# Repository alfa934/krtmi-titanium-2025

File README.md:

# 🤖TITANIUM (KRTMI) 2025 🤖

<p align="center"><b>📌Logo EIRRG dan TITANIUM📌</b></p>

## Deskripsi 📚
Kami adalah tim KRTMI (Kontes Robot Tematik Indonesia) dari Telkom University.  <br>
TITANIUM adalah nama tim kami.

## Anggota TITANIUM 2025 🏃‍♂️🏃‍♀️
| No | Nama | Nim | Jobdesk |
| :---: | :--- | :---: | :---: |
| 1 | Iki Tayubi | 1102223031 | Elektronika |
| 2 | Muhammad Aushaf Al Farras | 1102210215 | Program |
| 3 | Ahmad Fadhil Ghifari Ekaputra | 1102210053 | Program |
| 4 | Nabilla Rahma Anasya | 1104220025 | Official |
| 5 | Febrian Josua Kontu | 1102223066 | Program |
| 6 | Zahrani Cahya Priesa | 1103223074 | Official |
| 7 | Nurlina Sari | 1102223038 | Mekanik |
| 8 | Sarah Alexandra Siahaan | 1101220277 | Official |
| 9 | Muhammad Irfan Nabil | 1102223109 | Elektronika |
| 10 | Dimas Dwi Septian | 1102223106 | Mekanik |
| 11 | Muh. Ihksan Hatta | 1101223186 | Official |
| 12 | Valentine Rusliani Febriana | 102012300364 | Official |
| 13 | Ihsan Lisanul Arifin | 101022300309 | Mekanik |
| 14 | Muhammad Syauqi Fakhri | 101022330026 | Elektronika |
| 15 | Muhammad Miftah Faqih | 101022330177 | Program |
| 16 | Ivander Sugiarta Halim | 101022330111 | Elektronika |
| 17 | Mohammad Dzakwan Darrell Rifqi | 103032330138 | Program |
| 18 | Raditya Satria Pratama | 101032300096 | Program |
| 19 | Mohammad Hasbi Ashidiqi | 101022330302 | Mekanik |
| 20 | Raffa Ilyasa | 101022400260 | Elektronika |
| 21 | Wisnu Klana | 101022400118 | Official | 
| 22 | Brightly Jonah Aditya Santosa Padmohoetomo | 101022400074 | Program |
| 23 | Vincentius Radithya Evan Pratomo | 101062300011 | Mekanik | 

## Dosen Pembimbing 👨‍🏫👩‍🏫
| Pembimbing | Nama |
| :--- | :--- |
| Pembimbing 1 | Agung Surya Wibowo ,S.T.,M.T., Ph.D |
| Pembimbing 2 | Basith Abdurrohman Asy'ari, S.Tr.T., M.T. |

## KRTMI 2025 ??????
Tema : ?????? <br>
Jumlah Robot : ?????

## Sejarah KRTMI 📜
KRTMI pertama kali muncul tahun 2019, dan saat ini muncul 4 tema baru dari 2019 - 2024. <br>
Tujuannya untuk menyelesaikan masalah-masalah yang ada di Indonesia dengan teknologi bidang robotika.

## KRTMI 2024 (Robot Memilah Sampah) 🚮

Untuk lebih jelas, baca [Buku Panduan 2024](https://dit-mawa.upi.edu/wp-content/uploads/2024/01/Buku-Pedoman-KRI-2024-fix.pdf) halaman 133
### Video krtmi 2024
 <br>

## KRTMI 2021 - 2023 (Robo Game – Digital Twin) 🤖💻

Untuk lebih jelas, baca [Buku Panduan 2023](https://kontesrobotindonesia.id/data/2023/BukuPedomanKRI2023.pdf) halaman 125
### Video krtmi 2023
 <br>

## KRTMI 2020 (Robot Kesehatan) 😷👨‍⚕️👩‍⚕️

Untuk lebih jelas baca [Buku Panduan 2020](https://kontesrobotindonesia.id/data/2020/PetunjukPelaksanaanKRIDaring2020.pdf) halaman 79
### Video krtmi 2020
 <br>

## KRTMI 2019 (Robot Pertanian Padi) 🍚🌾

Untuk lebih jelas, baca [Buku Panduan 2019](https://kontesrobotindonesia.id/data/2019/Panduan_KRTMI2019.pdf) 
### Video krtmi 2019
 <br>

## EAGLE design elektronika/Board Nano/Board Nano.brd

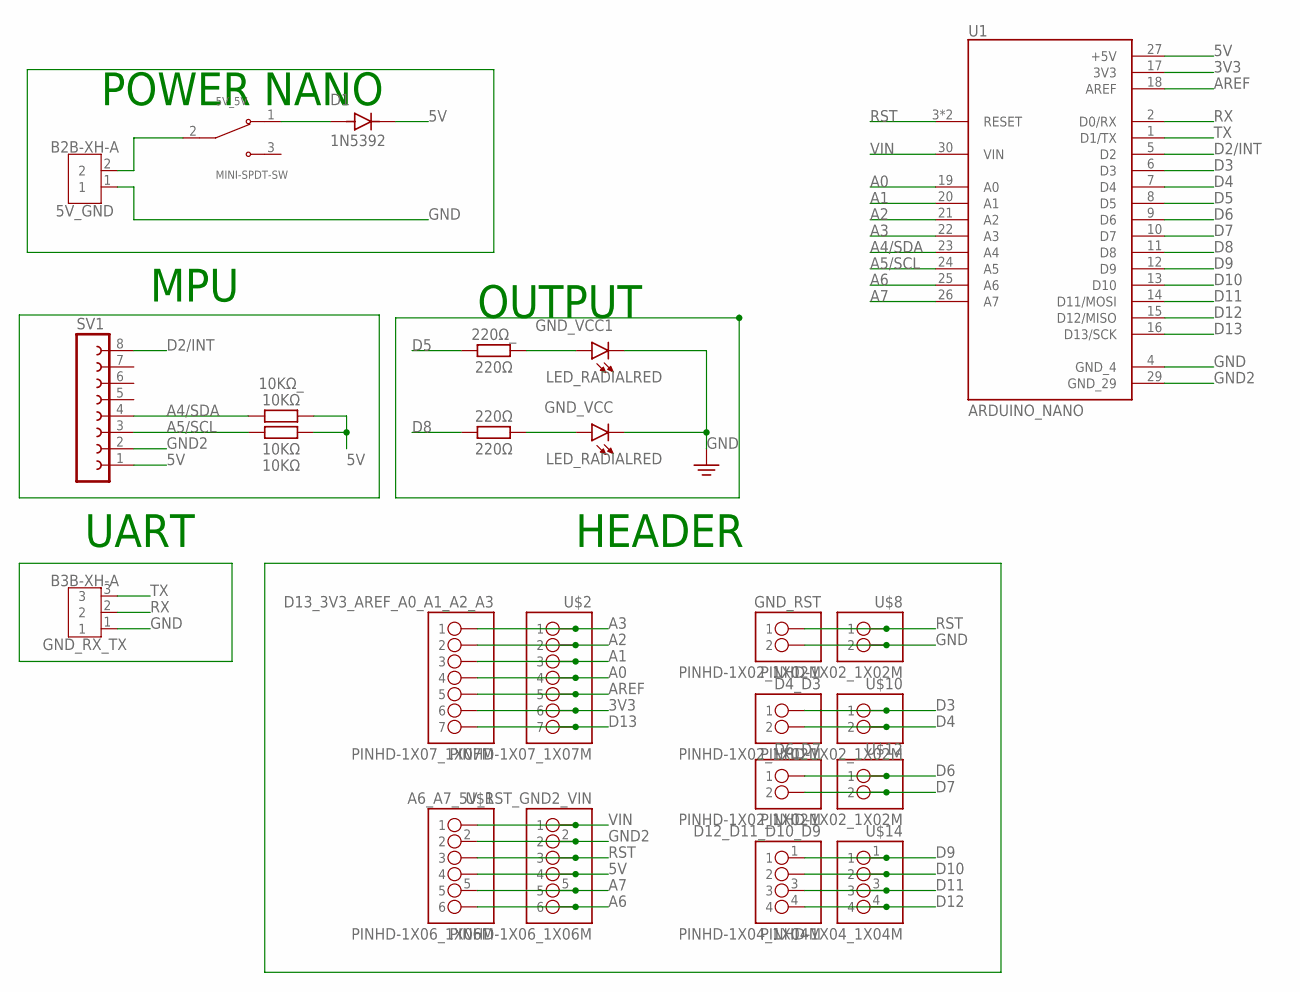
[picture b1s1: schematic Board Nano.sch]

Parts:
5V_5V: MINI-SPDT-SW; SW_MINI-SPDT-SW
5V_GND: B2B-XH-A
10KΩ, 10KΩ_: 10KΩ; RESAD1176W63L850D250B
220Ω, 220Ω_: 220Ω; RESAD1176W63L850D250B
A6_A7_5V_RST_GND2_VIN: PINHD-1X06_1X06M; 1X06
D1: 1N5392; DIOAD1300W80L670D310
D4_D3, D6_D7: PINHD-1X02_1X02M; 1X02
D12_D11_D10_D9: PINHD-1X04_1X04M; 1X04
D13_3V3_AREF_A0_A1_A2_A3: PINHD-1X07_1X07M; 1X07
GND_RST: PINHD-1X02_1X02M; 1X02
GND_RX_TX: B3B-XH-A
GND_VCC, GND_VCC1: LED_RADIALRED; LEDRD254W60D565H860B_R
SV1: FE08-1; FE08
U1: ARDUINO_NANO; MODULE_ARDUINO_NANO
U$1: PINHD-1X06_1X06M; 1X06
U$2: PINHD-1X07_1X07M; 1X07
U$8, U$10, U$12: PINHD-1X02_1X02M; 1X02
U$14: PINHD-1X04_1X04M; 1X04

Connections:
3V3: D13_3V3_AREF_A0_A1_A2_A3.6, U1.17 (3V3), U$2.6
5V: 10KΩ.2, 10KΩ_.2, A6_A7_5V_RST_GND2_VIN.4, D1.C (K), SV1.1, U1.27 (+5V), U$1.4
5V_FB: 5V_5V.2, 5V_GND.2
A0: D13_3V3_AREF_A0_A1_A2_A3.4, U1.19 (A0), U$2.4
A1: D13_3V3_AREF_A0_A1_A2_A3.3, U1.20 (A1), U$2.3
A2: D13_3V3_AREF_A0_A1_A2_A3.2, U1.21 (A2), U$2.2
A3: D13_3V3_AREF_A0_A1_A2_A3.1, U1.22 (A3), U$2.1
A4/SDA: 10KΩ_.1, SV1.4, U1.23 (A4)
A5/SCL: 10KΩ.1, SV1.3, U1.24 (A5)
A6: A6_A7_5V_RST_GND2_VIN.6, U1.25 (A6), U$1.6
A7: A6_A7_5V_RST_GND2_VIN.5, U1.26 (A7), U$1.5
AREF: D13_3V3_AREF_A0_A1_A2_A3.5, U1.18 (AREF), U$2.5
D2/INT: SV1.8, U1.5 (D2)
D3: D4_D3.1, U1.6 (D3), U$10.1
D4: D4_D3.2, U1.7 (D4), U$10.2
D5: 220Ω_.1, U1.8 (D5)
D6: D6_D7.1, U1.9 (D6), U$12.1
D7: D6_D7.2, U1.10 (D7), U$12.2
D8: 220Ω.1, U1.11 (D8)
D9: D12_D11_D10_D9.1, U1.12 (D9), U$14.1
D10: D12_D11_D10_D9.2, U1.13 (D10), U$14.2
D11: D12_D11_D10_D9.3, U1.14 (D11/MOSI), U$14.3
D12: D12_D11_D10_D9.4, U1.15 (D12/MISO), U$14.4
D13: D13_3V3_AREF_A0_A1_A2_A3.7, U1.16 (D13/SCK), U$2.7
GND: 5V_GND.1, GND_RST.2, GND_RX_TX.1, GND_VCC.C, GND_VCC1.C, U1.4 (GND_4), U$8.2
GND2: A6_A7_5V_RST_GND2_VIN.2, SV1.2, U1.29 (GND_29), U$1.2
unnamed: 220Ω_.2, GND_VCC1.A
unnamed: 220Ω.2, GND_VCC.A
unnamed: 5V_5V.1, D1.A
RST: A6_A7_5V_RST_GND2_VIN.3, GND_RST.1, U1.3 (RESET), U1.28 (RESET), U$1.3, U$8.1
RX: GND_RX_TX.2, U1.2 (D0/RX)
TX: GND_RX_TX.3, U1.1 (D1/TX)
VIN: A6_A7_5V_RST_GND2_VIN.1, U1.30 (VIN), U$1.1

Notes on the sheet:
POWER NANO
MPU
UART
OUTPUT
HEADER

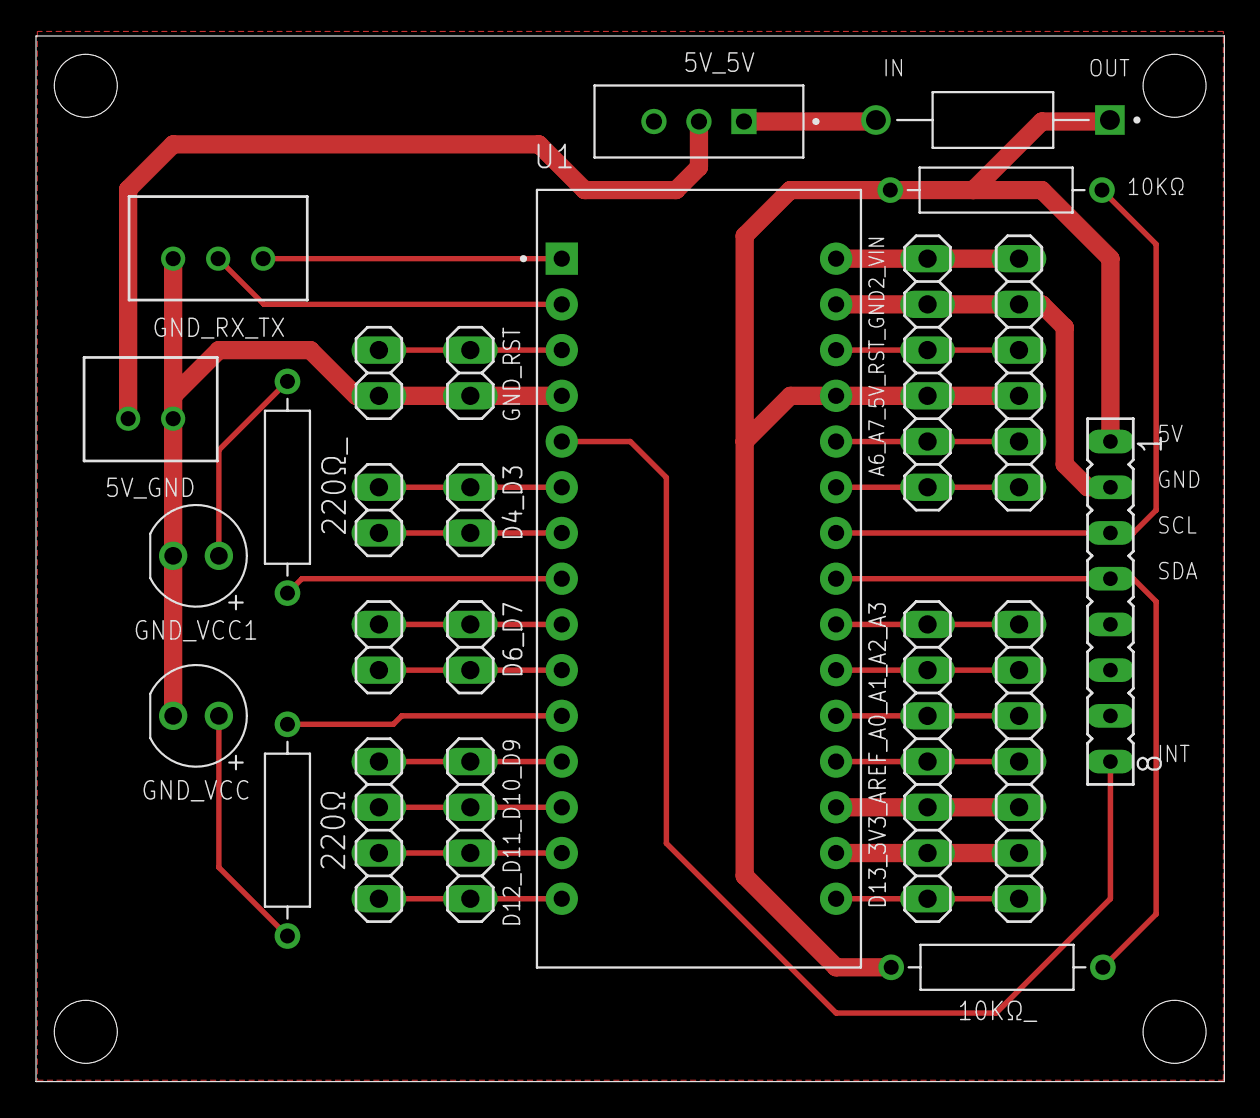
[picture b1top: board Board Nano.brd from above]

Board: 2 copper layers, 66.0 x 58.1 mm, 24 parts (0 on the bottom side), 33 nets.

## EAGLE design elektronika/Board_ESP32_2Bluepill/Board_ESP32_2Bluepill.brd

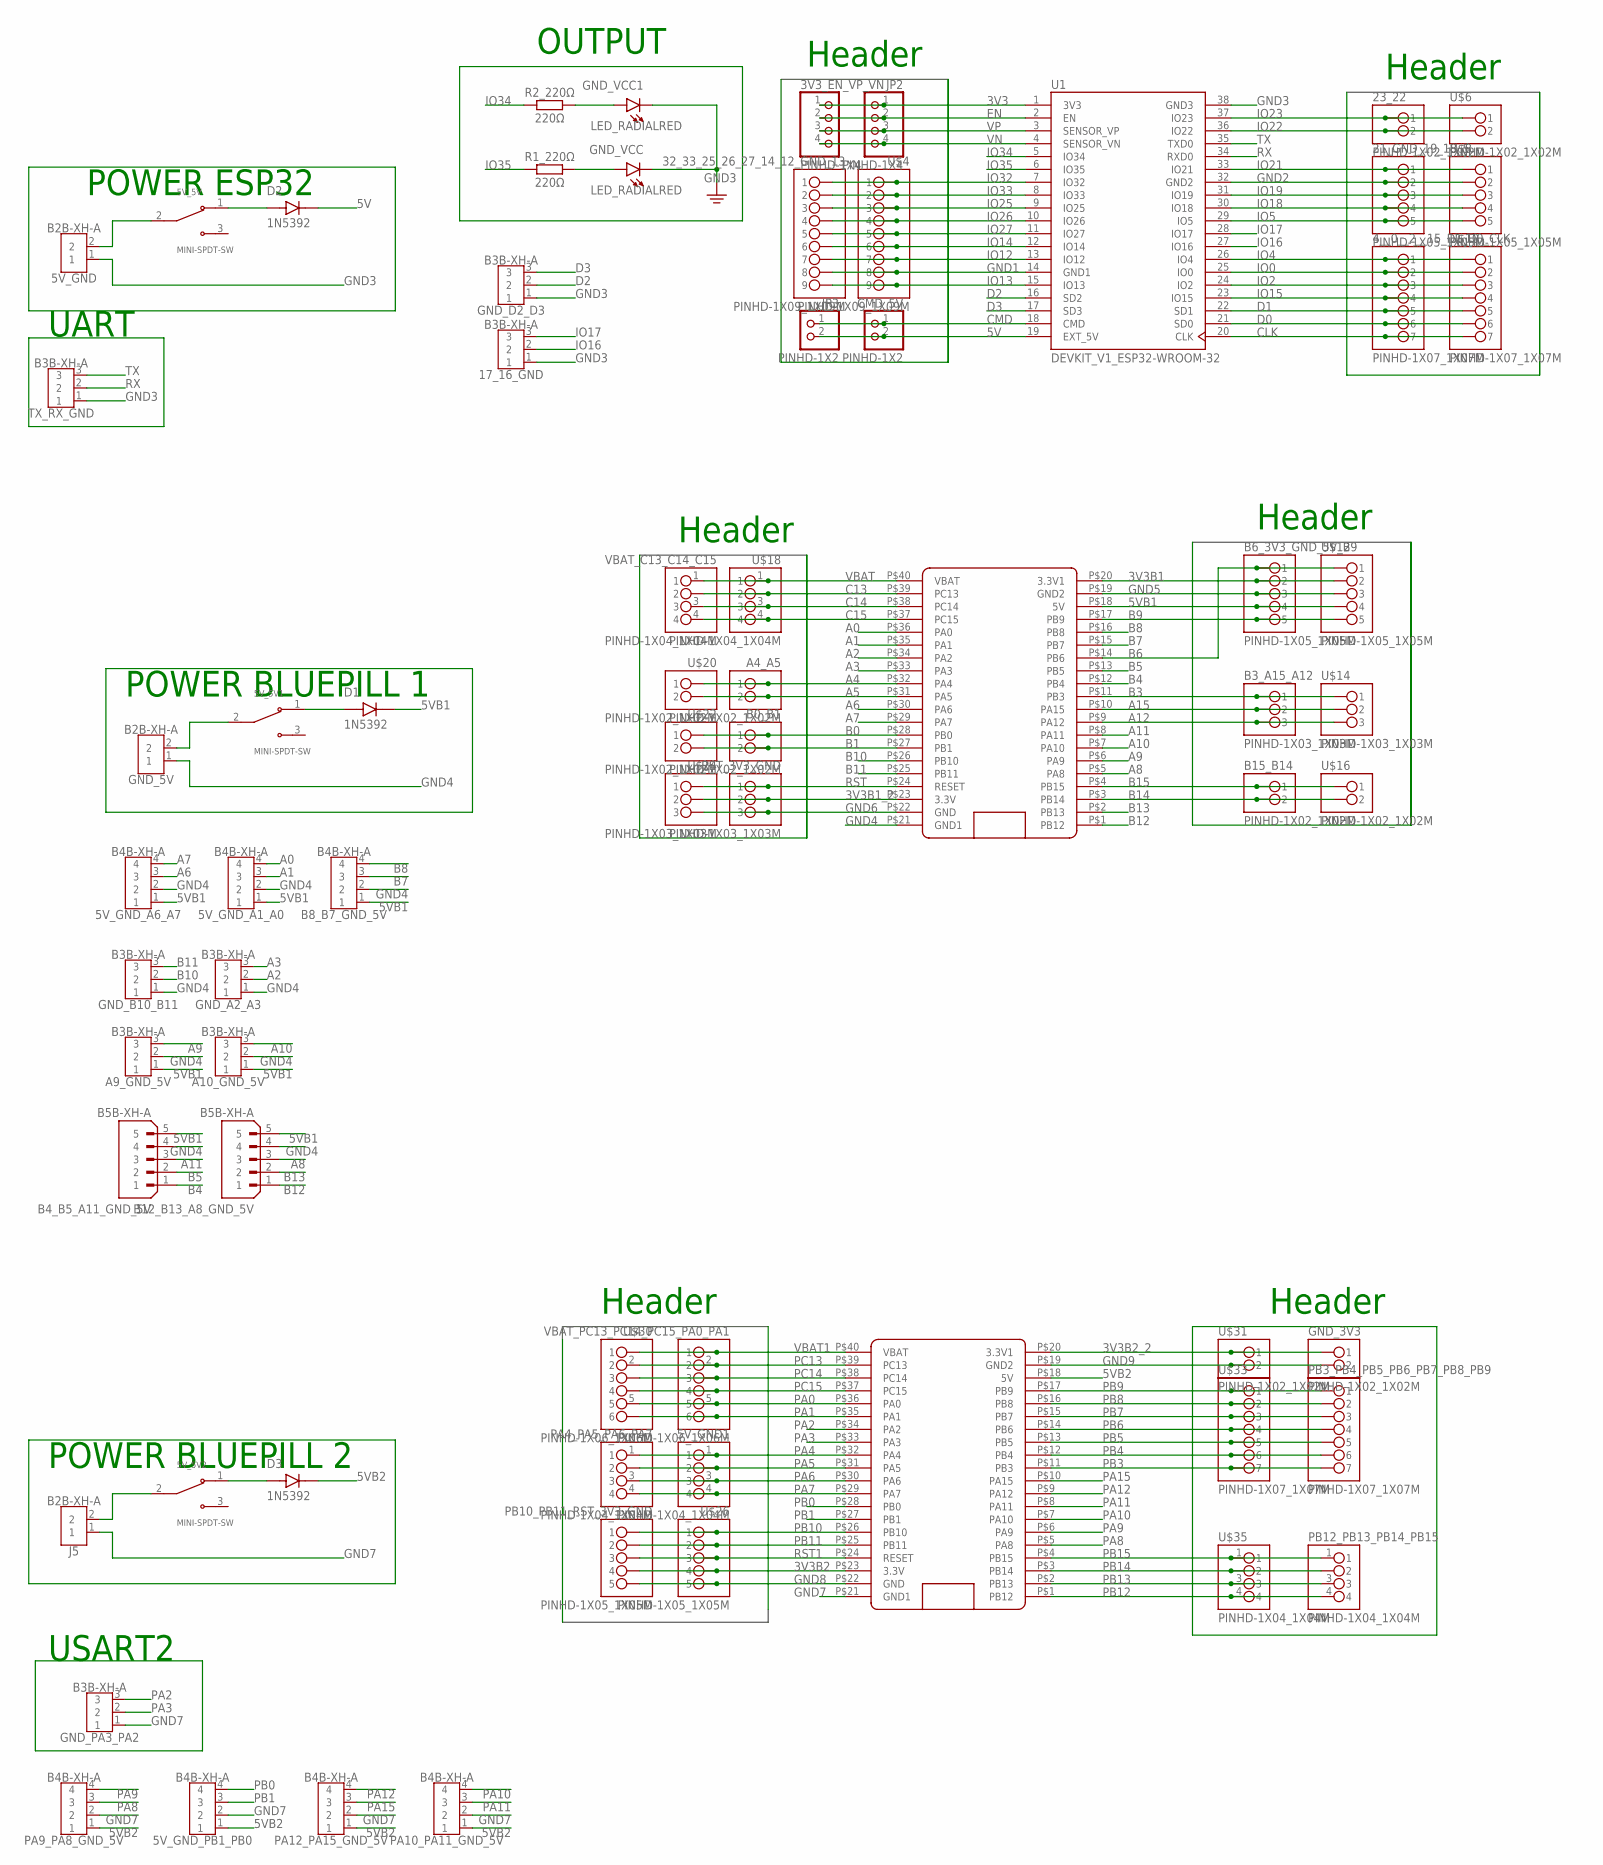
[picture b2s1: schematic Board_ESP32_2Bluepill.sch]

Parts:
3V3_EN_VP_VN: PINHD-1X4; 1X04
4__0__2__15_D1_D0_CLK: PINHD-1X07_1X07M; 1X07
5V_5V, 5V_5V1, 5V_5V2: MINI-SPDT-SW; SW_MINI-SPDT-SW
5V_GND: B2B-XH-A
5V_GND1: PINHD-1X04_1X04M; 1X04
5V_GND_A1_A0, 5V_GND_A6_A7, 5V_GND_PB1_PB0: B4B-XH-A
17_16_GND: B3B-XH-A
21_GND_19_18_5: PINHD-1X05_1X05M; 1X05
23_22: PINHD-1X02_1X02M; 1X02
32_33_25_26_27_14_12_GND_13: PINHD-1X09_1X09M; 1X09
A4_A5: PINHD-1X02_1X02M; 1X02
A9_GND_5V, A10_GND_5V: B3B-XH-A
B0_B1, B15_B14: PINHD-1X02_1X02M; 1X02
B3_A15_A12: PINHD-1X03_1X03M; 1X03
B4_B5_A11_GND_5V, B12_B13_A8_GND_5V: B5B-XH-A; JST_B5B-XH-A
B6_3V3_GND_5V_B9: PINHD-1X05_1X05M; 1X05
B8_B7_GND_5V: B4B-XH-A
CMD_5V: PINHD-1X2; 1X02
D1, D2, D3: 1N5392; DIOAD1300W80L670D310
GND_3V3: PINHD-1X02_1X02M; 1X02
GND_5V: B2B-XH-A
GND_A2_A3: B3B-XH-A
GND_B10_B11: B3B-XH-A
GND_D2_D3: B3B-XH-A
GND_PA3_PA2: B3B-XH-A
GND_VCC, GND_VCC1: LED_RADIALRED; LEDRD254W60D565H860B_R
J5: B2B-XH-A
JP2: PINHD-1X4; 1X04
JP3: PINHD-1X2; 1X02
PA4_PA5_PA6_PA7: PINHD-1X04_1X04M; 1X04
PA9_PA8_GND_5V, PA10_PA11_GND_5V, PA12_PA15_GND_5V: B4B-XH-A
PB3_PB4_PB5_PB6_PB7_PB8_PB9: PINHD-1X07_1X07M; 1X07
PB10_PB11_RST_3V3_GND: PINHD-1X05_1X05M; 1X05
PB12_PB13_PB14_PB15: PINHD-1X04_1X04M; 1X04
R1_220Ω, R2_220Ω: 220Ω; RESAD1176W63L850D250B
RST_3V3_GND: PINHD-1X03_1X03M; 1X03
TX_RX_GND: B3B-XH-A
U1: DEVKIT_V1_ESP32-WROOM-32; MODULE_DEVKIT_V1_ESP32-WROOM-32
U$1, U$2: BLUE_PILL
U$4: PINHD-1X09_1X09M; 1X09
U$6, U$16, U$20, U$22, U$31: PINHD-1X02_1X02M; 1X02
U$8, U$12, U$26: PINHD-1X05_1X05M; 1X05
U$10, U$33: PINHD-1X07_1X07M; 1X07
U$14, U$24: PINHD-1X03_1X03M; 1X03
U$18, U$35: PINHD-1X04_1X04M; 1X04
U$30: PINHD-1X06_1X06M; 1X06
VBAT_C13_C14_C15: PINHD-1X04_1X04M; 1X04
VBAT_PC13_PC14_PC15_PA0_PA1: PINHD-1X06_1X06M; 1X06

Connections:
3V3: 3V3_EN_VP_VN.1, JP2.1, U1.1 (3V3)
3V3B1: B6_3V3_GND_5V_B9.2, U$1.P$20 (3.3V1), U$12.2
3V3B1_2: RST_3V3_GND.2, U$1.P$23 (3.3V), U$24.2
3V3B2: PB10_PB11_RST_3V3_GND.4, U$2.P$23 (3.3V), U$26.4
3V3B2_2: GND_3V3.1, U$2.P$20 (3.3V1), U$31.1
5V: CMD_5V.2, D2.C (K), JP3.2, U1.19 (EXT_5V)
5VB1: 5V_GND_A1_A0.1, 5V_GND_A6_A7.1, A9_GND_5V.1, A10_GND_5V.1, B4_B5_A11_GND_5V.5, B6_3V3_GND_5V_B9.4, B8_B7_GND_5V.1, B12_B13_A8_GND_5V.5, D1.C (K), U$1.P$18 (5V), U$12.4
5VB2: 5V_GND_PB1_PB0.1, D3.C (K), PA9_PA8_GND_5V.1, PA10_PA11_GND_5V.1, PA12_PA15_GND_5V.1, U$2.P$18 (5V)
5V_FB1: 5V_5V.2, 5V_GND.2
5V_FB2: 5V_5V1.2, GND_5V.2
5V_FB3: 5V_5V2.2, J5.2
A0: 5V_GND_A1_A0.4, U$1.P$36 (PA0)
A1: 5V_GND_A1_A0.3, U$1.P$35 (PA1)
A2: GND_A2_A3.2, U$1.P$34 (PA2)
A3: GND_A2_A3.3, U$1.P$33 (PA3)
A4: A4_A5.1, U$1.P$32 (PA4), U$20.1
A5: A4_A5.2, U$1.P$31 (PA5), U$20.2
A6: 5V_GND_A6_A7.3, U$1.P$30 (PA6)
A7: 5V_GND_A6_A7.4, U$1.P$29 (PA7)
A8: B12_B13_A8_GND_5V.3, U$1.P$5 (PA8)
A9: A9_GND_5V.3, U$1.P$6 (PA9)
A10: A10_GND_5V.3, U$1.P$7 (PA10)
A11: B4_B5_A11_GND_5V.3, U$1.P$8 (PA11)
A12: B3_A15_A12.3, U$1.P$9 (PA12), U$14.3
A15: B3_A15_A12.2, U$1.P$10 (PA15), U$14.2
B0: B0_B1.1, U$1.P$28 (PB0), U$22.1
B1: B0_B1.2, U$1.P$27 (PB1), U$22.2
B3: B3_A15_A12.1, U$1.P$11 (PB3), U$14.1
B4: B4_B5_A11_GND_5V.1, U$1.P$12 (PB4)
B5: B4_B5_A11_GND_5V.2, U$1.P$13 (PB5)
B6: B6_3V3_GND_5V_B9.1, U$1.P$14 (PB6), U$12.1
B7: B8_B7_GND_5V.3, U$1.P$15 (PB7)
B8: B8_B7_GND_5V.4, U$1.P$16 (PB8)
B9: B6_3V3_GND_5V_B9.5, U$1.P$17 (PB9), U$12.5
B10: GND_B10_B11.2, U$1.P$26 (PB10)
B11: GND_B10_B11.3, U$1.P$25 (PB11)
B12: B12_B13_A8_GND_5V.1, U$1.P$1 (PB12)
B13: B12_B13_A8_GND_5V.2, U$1.P$2 (PB13)
B14: B15_B14.2, U$1.P$3 (PB14), U$16.2
B15: B15_B14.1, U$1.P$4 (PB15), U$16.1
C13: U$1.P$39 (PC13), U$18.2, VBAT_C13_C14_C15.2
C14: U$1.P$38 (PC14), U$18.3, VBAT_C13_C14_C15.3
C15: U$1.P$37 (PC15), U$18.4, VBAT_C13_C14_C15.4
CLK: 4__0__2__15_D1_D0_CLK.7, U1.20 (CLK), U$10.7
CMD: CMD_5V.1, JP3.1, U1.18 (CMD)
D0: 4__0__2__15_D1_D0_CLK.6, U1.21 (SD0), U$10.6
D1: 4__0__2__15_D1_D0_CLK.5, U1.22 (SD1), U$10.5
D2: GND_D2_D3.2, U1.16 (SD2)
D3: GND_D2_D3.3, U1.17 (SD3)
EN: 3V3_EN_VP_VN.2, JP2.2, U1.2 (EN)
GND1: 32_33_25_26_27_14_12_GND_13.8, U1.14 (GND1), U$4.8
GND2: 21_GND_19_18_5.2, U1.32 (GND2), U$8.2
GND3: 5V_GND.1, 17_16_GND.1, GND_D2_D3.1, GND_VCC.C, GND_VCC1.C, TX_RX_GND.1, U1.38 (GND3)
GND4: 5V_GND_A1_A0.2, 5V_GND_A6_A7.2, A9_GND_5V.2, A10_GND_5V.2, B4_B5_A11_GND_5V.4, B8_B7_GND_5V.2, B12_B13_A8_GND_5V.4, GND_5V.1, GND_A2_A3.1, GND_B10_B11.1, U$1.P$21 (GND1)
GND5: B6_3V3_GND_5V_B9.3, U$1.P$19 (GND2), U$12.3
GND6: RST_3V3_GND.3, U$1.P$22 (GND), U$24.3
GND7: 5V_GND_PB1_PB0.2, GND_PA3_PA2.1, J5.1, PA9_PA8_GND_5V.2, PA10_PA11_GND_5V.2, PA12_PA15_GND_5V.2, U$2.P$21 (GND1)
GND8: PB10_PB11_RST_3V3_GND.5, U$2.P$22 (GND), U$26.5
GND9: GND_3V3.2, U$2.P$19 (GND2), U$31.2
IO0: 4__0__2__15_D1_D0_CLK.2, U1.25 (IO0), U$10.2
IO2: 4__0__2__15_D1_D0_CLK.3, U1.24 (IO2), U$10.3
IO4: 4__0__2__15_D1_D0_CLK.1, U1.26 (IO4), U$10.1
IO5: 21_GND_19_18_5.5, U1.29 (IO5), U$8.5
IO12: 32_33_25_26_27_14_12_GND_13.7, U1.13 (IO12), U$4.7
IO13: 32_33_25_26_27_14_12_GND_13.9, U1.15 (IO13), U$4.9
IO14: 32_33_25_26_27_14_12_GND_13.6, U1.12 (IO14), U$4.6
IO15: 4__0__2__15_D1_D0_CLK.4, U1.23 (IO15), U$10.4
IO16: 17_16_GND.2, U1.27 (IO16)
IO17: 17_16_GND.3, U1.28 (IO17)
IO18: 21_GND_19_18_5.4, U1.30 (IO18), U$8.4
IO19: 21_GND_19_18_5.3, U1.31 (IO19), U$8.3
IO21: 21_GND_19_18_5.1, U1.33 (IO21), U$8.1
IO22: 23_22.2, U1.36 (IO22), U$6.2
IO23: 23_22.1, U1.37 (IO23), U$6.1
IO25: 32_33_25_26_27_14_12_GND_13.3, U1.9 (IO25), U$4.3
IO26: 32_33_25_26_27_14_12_GND_13.4, U1.10 (IO26), U$4.4
IO27: 32_33_25_26_27_14_12_GND_13.5, U1.11 (IO27), U$4.5
IO32: 32_33_25_26_27_14_12_GND_13.1, U1.7 (IO32), U$4.1
IO33: 32_33_25_26_27_14_12_GND_13.2, U1.8 (IO33), U$4.2
IO34: R2_220Ω.1, U1.5 (IO34)
IO35: R1_220Ω.1, U1.6 (IO35)
unnamed: GND_VCC1.A, R2_220Ω.2
unnamed: GND_VCC.A, R1_220Ω.2
unnamed: 5V_5V.1, D2.A
unnamed: 5V_5V2.1, D3.A
unnamed: 5V_5V1.1, D1.A
PA0: U$2.P$36 (PA0), U$30.5, VBAT_PC13_PC14_PC15_PA0_PA1.5
PA1: U$2.P$35 (PA1), U$30.6, VBAT_PC13_PC14_PC15_PA0_PA1.6
PA2: GND_PA3_PA2.3, U$2.P$34 (PA2)
PA3: GND_PA3_PA2.2, U$2.P$33 (PA3)
PA4: 5V_GND1.1, PA4_PA5_PA6_PA7.1, U$2.P$32 (PA4)
PA5: 5V_GND1.2, PA4_PA5_PA6_PA7.2, U$2.P$31 (PA5)
PA6: 5V_GND1.3, PA4_PA5_PA6_PA7.3, U$2.P$30 (PA6)
PA7: 5V_GND1.4, PA4_PA5_PA6_PA7.4, U$2.P$29 (PA7)
PA8: PA9_PA8_GND_5V.3, U$2.P$5 (PA8)
PA9: PA9_PA8_GND_5V.4, U$2.P$6 (PA9)
PA10: PA10_PA11_GND_5V.4, U$2.P$7 (PA10)
PA11: PA10_PA11_GND_5V.3, U$2.P$8 (PA11)
PA12: PA12_PA15_GND_5V.4, U$2.P$9 (PA12)
PA15: PA12_PA15_GND_5V.3, U$2.P$10 (PA15)
PB0: 5V_GND_PB1_PB0.4, U$2.P$28 (PB0)
PB1: 5V_GND_PB1_PB0.3, U$2.P$27 (PB1)
PB3: PB3_PB4_PB5_PB6_PB7_PB8_PB9.7, U$2.P$11 (PB3), U$33.7
PB4: PB3_PB4_PB5_PB6_PB7_PB8_PB9.6, U$2.P$12 (PB4), U$33.6
PB5: PB3_PB4_PB5_PB6_PB7_PB8_PB9.5, U$2.P$13 (PB5), U$33.5
PB6: PB3_PB4_PB5_PB6_PB7_PB8_PB9.4, U$2.P$14 (PB6), U$33.4
PB7: PB3_PB4_PB5_PB6_PB7_PB8_PB9.3, U$2.P$15 (PB7), U$33.3
PB8: PB3_PB4_PB5_PB6_PB7_PB8_PB9.2, U$2.P$16 (PB8), U$33.2
PB9: PB3_PB4_PB5_PB6_PB7_PB8_PB9.1, U$2.P$17 (PB9), U$33.1
PB10: PB10_PB11_RST_3V3_GND.1, U$2.P$26 (PB10), U$26.1
PB11: PB10_PB11_RST_3V3_GND.2, U$2.P$25 (PB11), U$26.2
PB12: PB12_PB13_PB14_PB15.4, U$2.P$1 (PB12), U$35.4
PB13: PB12_PB13_PB14_PB15.3, U$2.P$2 (PB13), U$35.3
PB14: PB12_PB13_PB14_PB15.2, U$2.P$3 (PB14), U$35.2
PB15: PB12_PB13_PB14_PB15.1, U$2.P$4 (PB15), U$35.1
PC13: U$2.P$39 (PC13), U$30.2, VBAT_PC13_PC14_PC15_PA0_PA1.2
PC14: U$2.P$38 (PC14), U$30.3, VBAT_PC13_PC14_PC15_PA0_PA1.3
PC15: U$2.P$37 (PC15), U$30.4, VBAT_PC13_PC14_PC15_PA0_PA1.4
RST: RST_3V3_GND.1, U$1.P$24 (RESET), U$24.1
RST1: PB10_PB11_RST_3V3_GND.3, U$2.P$24 (RESET), U$26.3
RX: TX_RX_GND.2, U1.34 (RXD0)
TX: TX_RX_GND.3, U1.35 (TXD0)
VBAT: U$1.P$40 (VBAT), U$18.1, VBAT_C13_C14_C15.1
VBAT1: U$2.P$40 (VBAT), U$30.1, VBAT_PC13_PC14_PC15_PA0_PA1.1
VN: 3V3_EN_VP_VN.4, JP2.4, U1.4 (SENSOR_VN)
VP: 3V3_EN_VP_VN.3, JP2.3, U1.3 (SENSOR_VP)

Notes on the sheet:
POWER ESP32
POWER BLUEPILL 1
POWER BLUEPILL 2
OUTPUT
Header
USART2
UART

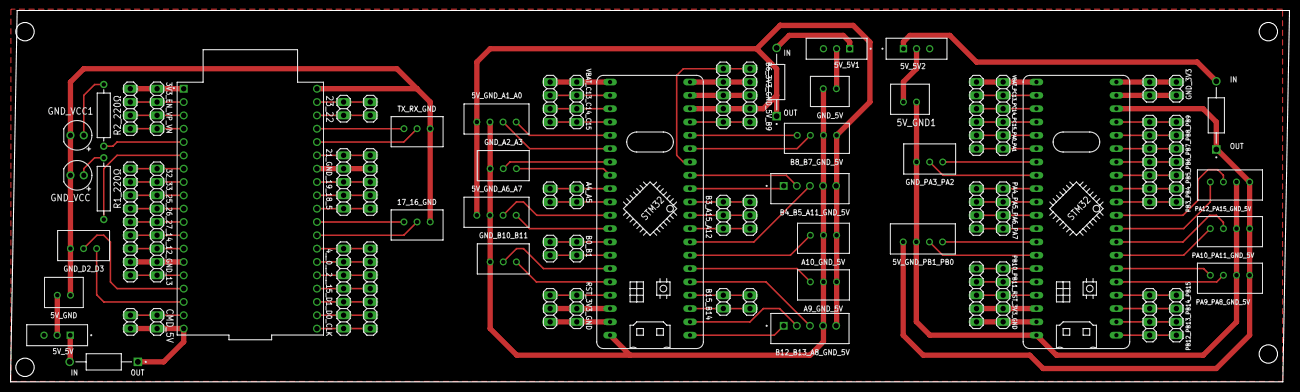
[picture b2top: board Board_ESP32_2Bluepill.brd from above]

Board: 2 copper layers, 243.8 x 70.8 mm, 71 parts (0 on the bottom side), 126 nets.

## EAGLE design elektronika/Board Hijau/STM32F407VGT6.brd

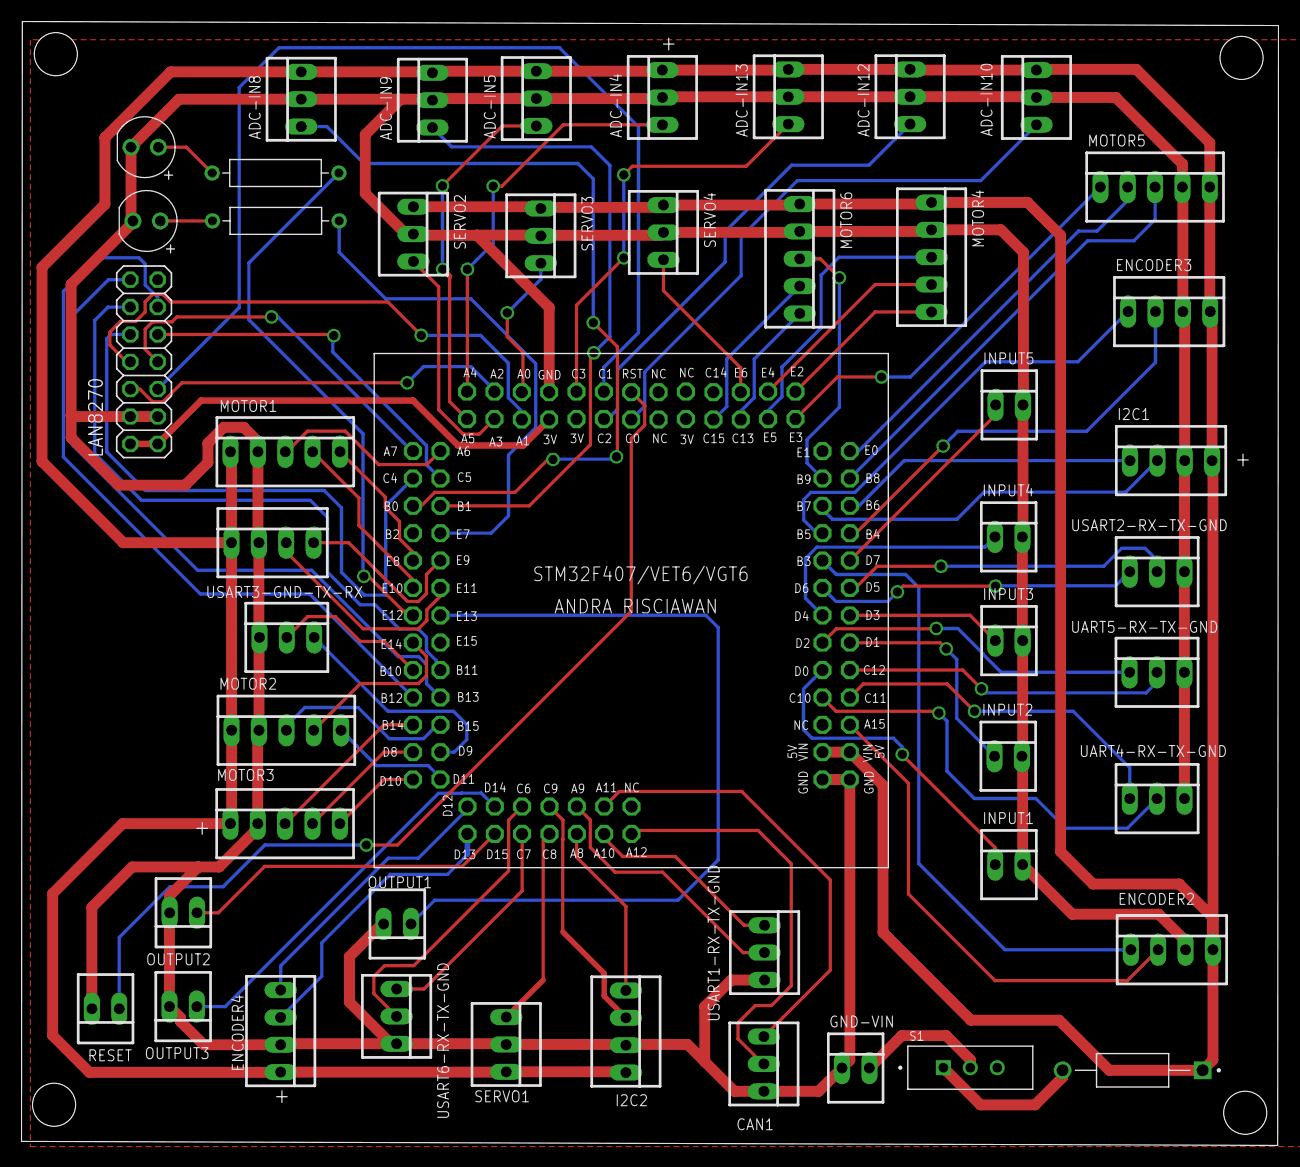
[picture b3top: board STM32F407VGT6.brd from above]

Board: 2 copper layers, 116.7 x 104.3 mm, 48 parts (0 on the bottom side), 82 nets.

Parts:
ADC-IN4, ADC-IN5, ADC-IN8, ADC-IN9, ADC-IN10, ADC-IN12, ADC-IN13: 22-23-2031
CAN1: 22-23-2031
D1, D2: LED_RADIALRED; LEDRD254W60D565H860B_R
D4: 1N5392; DIOAD1300W80L670D310
ENCODER1, ENCODER2, ENCODER3, ENCODER4: 22-23-2041
GND-VIN: 22-23-2021
I2C1, I2C2: 22-23-2041
INPUT1, INPUT2, INPUT3, INPUT4, INPUT5: 22-23-2021
LAN8270: PINHD-2X7; 2X07
MOTOR1, MOTOR2, MOTOR3, MOTOR4, MOTOR5, MOTOR6: 22-23-2051
OUTPUT1, OUTPUT2, OUTPUT3: 22-23-2021
R1, R2: RESAD1176W63L850D250B
RESET: 22-23-2021
S1: MINI-SPDT-SW; SW_MINI-SPDT-SW
SERVO1, SERVO2, SERVO3, SERVO4: 22-23-2031
U$1: STM32F4HEAD
UART4-RX-TX-GND, UART5-RX-TX-GND: 22-23-2031
USART1-RX-TX-GND, USART2-RX-TX-GND, USART3-GND-TX-RX, USART6-RX-TX-GND: 22-23-2031

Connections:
3V3: LAN8270.1, LAN8270.2, U$1.3V1, U$1.3V2, U$1.3V3
5V: ADC-IN4.3, ADC-IN5.3, ADC-IN8.3, ADC-IN9.3, ADC-IN10.3, ADC-IN12.3, ADC-IN13.3, D4.C, ENCODER1.1, ENCODER2.4, ENCODER3.4, ENCODER4.4, I2C1.4, I2C2.4, MOTOR1.1, MOTOR2.1, MOTOR3.1, MOTOR4.1, MOTOR5.5, MOTOR6.1, SERVO1.3, SERVO2.1, SERVO3.1, SERVO4.1, U$1.5V1, U$1.5V2
CRS_DV: LAN8270.7, U$1.A7
GND: ADC-IN4.2, ADC-IN5.2, ADC-IN8.2, ADC-IN9.2, ADC-IN10.2, ADC-IN12.2, ADC-IN13.2, CAN1.3, D1.C, D2.C, ENCODER1.2, ENCODER2.3, ENCODER3.3, ENCODER4.3, GND-VIN.1, I2C1.3, I2C2.3, INPUT1.2, INPUT2.2, INPUT3.2, INPUT4.2, INPUT5.2, LAN8270.3, LAN8270.4, MOTOR1.2, MOTOR2.2, MOTOR3.2, MOTOR4.2, MOTOR5.4, MOTOR6.2, OUTPUT1.2, OUTPUT2.2, OUTPUT3.2, RESET.2, SERVO1.2, SERVO2.2, SERVO3.2, SERVO4.2, U$1.GND1, U$1.GND2, U$1.GND3, UART4-RX-TX-GND.3, UART5-RX-TX-GND.3, USART1-RX-TX-GND.3, USART2-RX-TX-GND.3, USART3-GND-TX-RX.1, USART6-RX-TX-GND.3
MDC: LAN8270.5, U$1.C1
MDIO: LAN8270.6, U$1.A2
unnamed: D4.A, S1.1
unnamed: GND-VIN.2, S1.2
unnamed: D1.A, R1.2
unnamed: D2.A, R2.2
PA0: SERVO3.3, U$1.A0
PA3: SERVO2.3, U$1.A3
PA4: ADC-IN4.1, U$1.A4
PA5: ADC-IN5.1, U$1.A5
PA6: MOTOR1.3, U$1.A6
PA9: U$1.A9, USART1-RX-TX-GND.2
PA10: U$1.A10, USART1-RX-TX-GND.1
PA15: ENCODER2.2, U$1.A15
PB0: ADC-IN8.1, U$1.B0
PB1: ADC-IN9.1, U$1.B1
PB3: ENCODER2.1, U$1.B3
PB4: ENCODER3.2, U$1.B4
PB5: ENCODER3.1, U$1.B5
PB8: MOTOR5.3, U$1.B8
PB9: MOTOR6.3, U$1.B9
PB10: U$1.B10, USART3-GND-TX-RX.2
PB14: MOTOR3.3, U$1.B14
PB15: MOTOR2.3, U$1.B15
PC0: ADC-IN10.1, U$1.C0
PC2: ADC-IN12.1, U$1.C2
PC3: ADC-IN13.1, U$1.C3
PC6: U$1.C6, USART6-RX-TX-GND.2
PC7: U$1.C7, USART6-RX-TX-GND.1
PC8: SERVO1.1, U$1.C8
PC10: U$1.C10, UART4-RX-TX-GND.2
PC11: U$1.C11, UART4-RX-TX-GND.1
PC12: U$1.C12, UART5-RX-TX-GND.2
PC13: MOTOR6.5, U$1.C13
PC15: MOTOR6.4, U$1.C15
PD0: INPUT1.1, U$1.D0
PD1: INPUT2.1, U$1.D1
PD2: U$1.D2, UART5-RX-TX-GND.1
PD3: INPUT3.1, U$1.D3
PD4: INPUT4.1, U$1.D4
PD5: U$1.D5, USART2-RX-TX-GND.2
PD6: U$1.D6, USART2-RX-TX-GND.1
PD7: INPUT5.1, U$1.D7
PD8: MOTOR3.4, U$1.D8
PD9: U$1.D9, USART3-GND-TX-RX.3
PD10: MOTOR3.5, U$1.D10
PD11: MOTOR2.5, U$1.D11
PD12: ENCODER4.1, U$1.D12
PD13: ENCODER4.2, U$1.D13
PD14: OUTPUT3.1, U$1.D14
PD15: OUTPUT2.1, U$1.D15
PE0: MOTOR5.2, U$1.E0
PE2: MOTOR4.5, U$1.E2
PE3: MOTOR5.1, U$1.E3
PE4: MOTOR4.4, U$1.E4
PE5: MOTOR4.3, U$1.E5
PE6: SERVO4.3, U$1.E6
PE7: R1.1, U$1.E7
PE8: MOTOR1.5, U$1.E8
PE9: ENCODER1.4, U$1.E9
PE10: MOTOR1.4, U$1.E10
PE11: ENCODER1.3, U$1.E11
PE12: R2.1, U$1.E12
PE13: OUTPUT1.1, U$1.E13
PE14: MOTOR2.4, U$1.E14
REF_CLK: LAN8270.8, U$1.A1
RST: RESET.1, U$1.RST
RX1: CAN1.1, U$1.A11
RXD0: LAN8270.10, U$1.C4
RXD1: LAN8270.9, U$1.C5
SCL1: I2C1.1, U$1.B6
SCL2: I2C2.1, U$1.A8
SDA1: I2C1.2, U$1.B7
SDA2: I2C2.2, U$1.C9
TX1: CAN1.2, U$1.A12
TXD0: LAN8270.11, U$1.B12
TXD1: LAN8270.14, U$1.B13
TX_EN: LAN8270.12, U$1.B11

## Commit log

2025-05-13 Rename Sosialisasi KRTMI 2024.pdf to src/Sosialisasi KRTMI 2024.pdf
2025-05-15 Rename log-2025-05-15.md to log-2025-05-15.md
2025-05-16 log-2025-05-15.md
2025-05-16 IMG_7334-powy.jpeg
2025-05-16 IMG_6042-Febrian.jpeg
2025-05-19 Rename elektronika/Board Hijau/schematic ijo.pdf to elektronika/2025-05-16/media/schematic ijo.pdf
2025-05-19 Rename elektronika/Board Hijau/STM32F407VGT6.brd to elektronika/2025-05-16/media/STM32F407VGT6.brd
2025-05-19 Rename elektronika/Board Hijau/STM32F407VGT6.f3z to elektronika/2025-05-16/media/STM32F407VGT6.f3z
2025-05-19 Rename elektronika/Board Hijau/STM32F407VGT6.sch to elektronika/2025-05-16/media/STM32F407VGT6.sch
2025-07-06 Create Power Management
2025-07-06 Create cihuyy
2025-07-06 Create Board ESP32 & 2Bluepill
2025-07-22 Create Canva
2025-07-22 Update Canva
